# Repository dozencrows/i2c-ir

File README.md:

i2c-ir
======
This is a program for the NXP LPC810 ARM microcontroller that makes it act as an IR remote
control code sender.

It implements a basic controlling interface using I2C, where the master device can send
packets of data to set the timing, length, repeat count and delay between repeats for
a single IR remote control code.

The IR signals generated consist of variable duration pulses of a 38kHz square wave,
interleaved with variable duration gaps.

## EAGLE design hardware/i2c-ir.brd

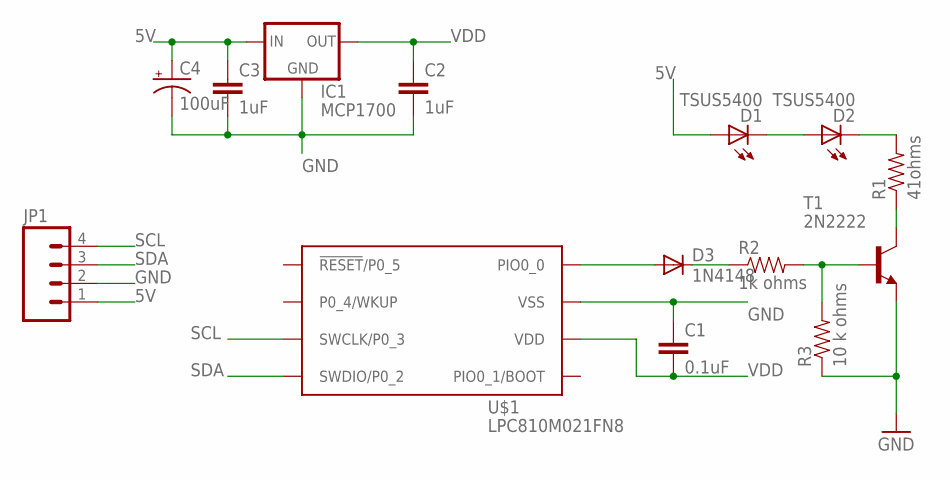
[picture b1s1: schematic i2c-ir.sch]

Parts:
C1: 0.1uF; CAP-PTH-SMALL
C2, C3: 1uF; CAP-PTH-SMALL
C4: 100uF; CPOL-RADIAL-100UF-25V
D1, D2: TSUS5400; SFH482
D3: 1N4148; DO35-7
IC1: MCP1700; TO92-INLINE
JP1: M04PTH; 1X04
R1: 41ohms; AXIAL-0.3
R2: 1k ohms; AXIAL-0.3
R3: 10 k ohms; AXIAL-0.3
T1: 2N2222; TO92-EBC-OVAL
U$1: LPC810M021FN8; DIP8

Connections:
5V: C3.1, C4.1 (+), D1.A, IC1.2 (IN), JP1.1
GND: C1.1, C2.2, C3.2, C4.2 (-), IC1.1 (GND), JP1.2, R3.P$1 (1), T1.E, U$1.P$7 (VSS)
unnamed: D1.K (C), D2.A
unnamed: D2.K (C), R1.P$2 (2)
unnamed: R1.P$1 (1), T1.C
unnamed: D3.A, U$1.P$8 (PIO0_0)
unnamed: D3.C, R2.P$1 (1)
unnamed: R2.P$2 (2), R3.P$2 (2), T1.B
SCL: JP1.4, U$1.P$3 (SWCLK/P0_3)
SDA: JP1.3, U$1.P$4 (SWDIO/P0_2)
VDD: C1.2, C2.1, IC1.3 (OUT), U$1.P$6 (VDD)

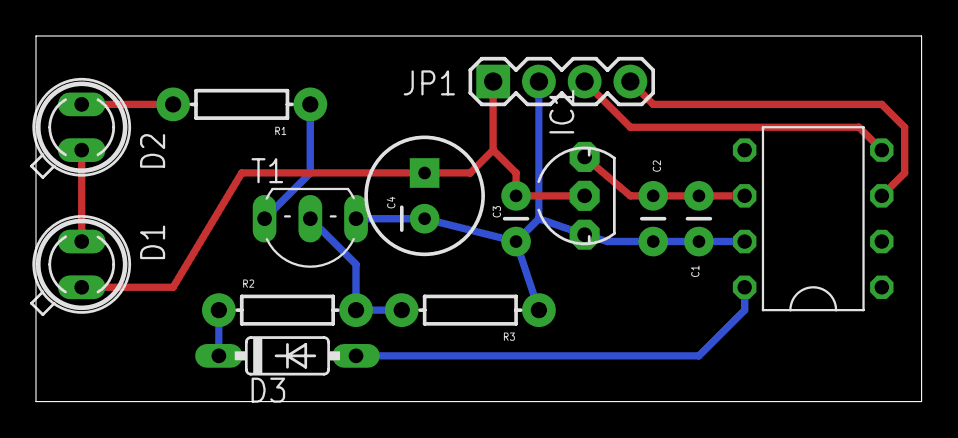
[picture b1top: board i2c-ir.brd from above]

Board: 2 copper layers, 49.2 x 20.3 mm, 14 parts (0 on the bottom side), 11 nets.

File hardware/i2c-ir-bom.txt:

Partlist exported from /home/ntuckett/Documents/eagle/pimony/lpc-ir/i2c-ir.sch at 12/04/2015 11:01

Qty Value         Device            Package               Parts  Description         
1                 M04PTH            1X04                  JP1    Header 4            
1   0.1uF         CAPPTH            CAP-PTH-SMALL         C1     Capacitor           
1   10 k ohms     RESISTORAXIAL-0.3 AXIAL-0.3             R3     Resistor            
1   100uF         CAP_POLPTH1       CPOL-RADIAL-100UF-25V C4     Capacitor Polarized 
1   1N4148        1N4148DO35-7      DO35-7                D3     DIODE               
1   1k ohms       RESISTORAXIAL-0.3 AXIAL-0.3             R2     Resistor            
2   1uF           CAPPTH            CAP-PTH-SMALL         C2, C3 Capacitor           
1   2N2222        2N2222            TO92-EBC-OVAL         T1     NPN TRANSISTOR      
1   41ohms        RESISTORAXIAL-0.3 AXIAL-0.3             R1     Resistor            
1   LPC810M021FN8 LPC810M021FN8     DIP8                  U$1                        
1   MCP1700       MCP1700INLINE     TO92-INLINE           IC1    VOLTAGE REGULATOR   
2   TSUS5400      SFH482            SFH482                D1, D2 IR LED

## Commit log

2015-02-09 Initial commit: baseline from i2clisten
2015-02-09 Tidyup unwanted stuff
2015-02-09 Fixup makefile
2015-02-09 Converted to basic I2C slave demo
2015-02-10 Configured 10Mhz clock using PLL
2015-02-11 Added SCT-driven square wave
2015-02-12 WIP: modulating square wave by second timer
2015-02-14 WIP on modulating timer L 38kHz square wave with timer H
2015-02-15 H timer now modulates L timer square wave accurately
2015-02-15 Drive output from buffer of timings
2015-02-15 Fixed ms delay timer; implemented repeat sends with inter-delay
2015-02-17 H timer prescale now 10 to divide down to microsecond values
2015-02-17 WIP: controlling IR output via I2C sent data
2015-02-21 WIP: custom I2C slave driver
2015-02-21 First working version with registers settable via I2C, and status register readback
2015-02-21 Added i2c tools test commands
2015-02-22 Added license
2015-02-22 Created README.
2015-02-22 Added copyright message; removed redundant header
2015-02-22 Corrected copyright message
2015-03-08 Put LPC into deep sleep when idle; wakes on I2C
2015-03-08 Switched to power down instead of deep sleep
2015-04-08 Implemented delayed sleep for better response time
2015-04-08 Switch to zero-wait-states for Flash for a little better performance
2015-04-08 Switched to O3 optimisations
2015-04-11 Fixed UART stoppage on reset
2015-04-11 Switched back to size optimised; not much gain on O3
2015-04-11 Tied down some floating outputs
2015-04-12 Switched IR control pin to PIO0_0
2015-04-12 Added basic PCB files
2015-05-03 Made makefile rules transportable
2015-06-20 Added more Eagle files

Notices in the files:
parts and their libraries:
SparkFun-Passives: Licensing: Creative Commons ShareAlike 4.0 International - https://creativecommons.org/licenses/by-sa/4.0
